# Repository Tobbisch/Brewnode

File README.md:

# Brewnode
Cheap IO node for taking in values to a Siemens PLC

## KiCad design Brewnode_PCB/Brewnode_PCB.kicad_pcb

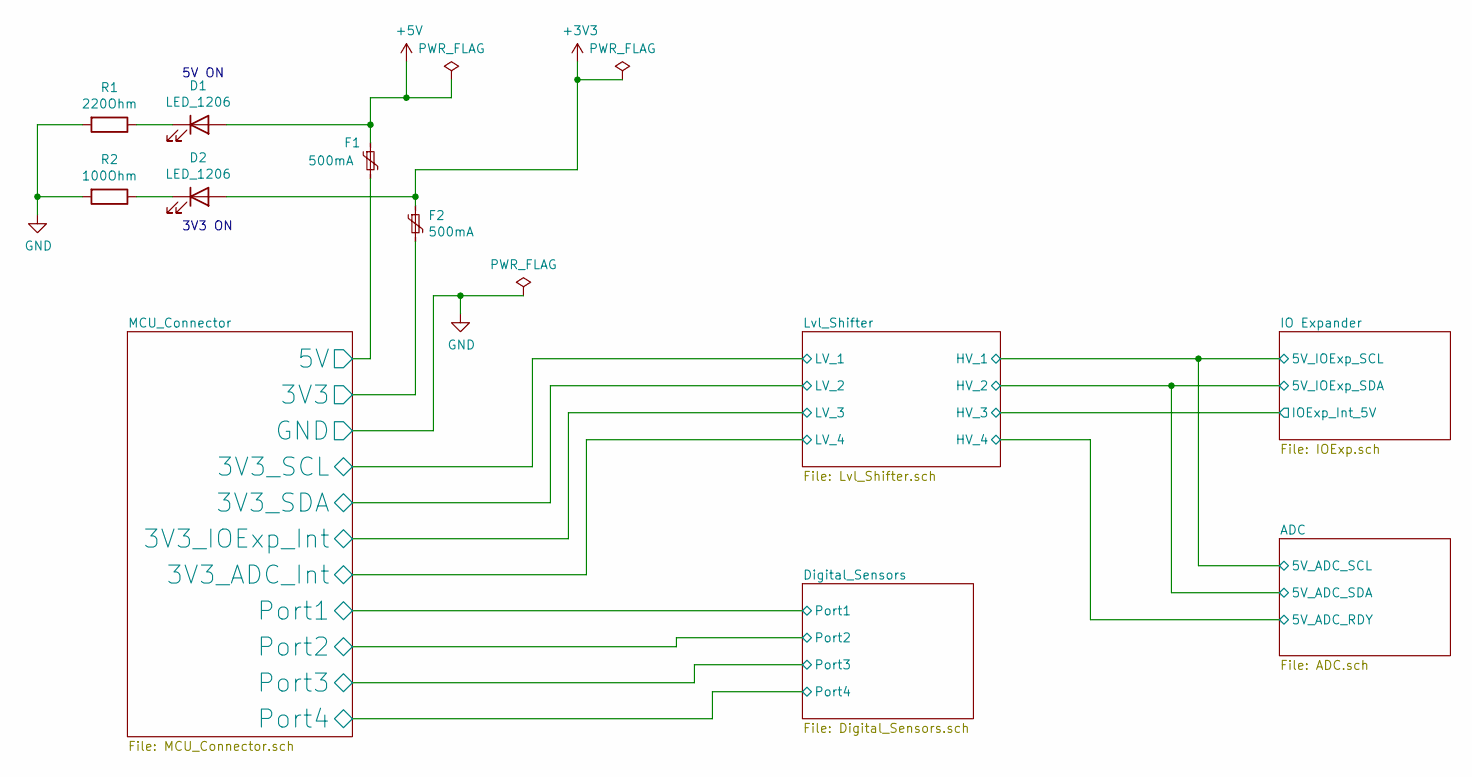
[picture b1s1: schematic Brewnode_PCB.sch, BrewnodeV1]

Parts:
D1, D2: LED_1206; LED_1206_3216Metric; LCSC C125085
F1, F2: 500mA; Fuse_0402_1005Metric; LCSC C206945
R1: 220Ohm; R_0805_2012Metric_Pad1.15x1.40mm_HandSolder; LCSC C17557
R2: 100Ohm; R_0805_2012Metric_Pad1.15x1.40mm_HandSolder; LCSC C17408

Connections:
/MCU_Connector/3V3: F2.2; also elsewhere on the board
/MCU_Connector/5V: F1.2; also elsewhere on the board
GND: R1.2, R2.2; also elsewhere on the board
unnamed: D1.1 (K), R1.1
unnamed: D2.1 (K), R2.1

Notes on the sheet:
5V ON
3V3 ON

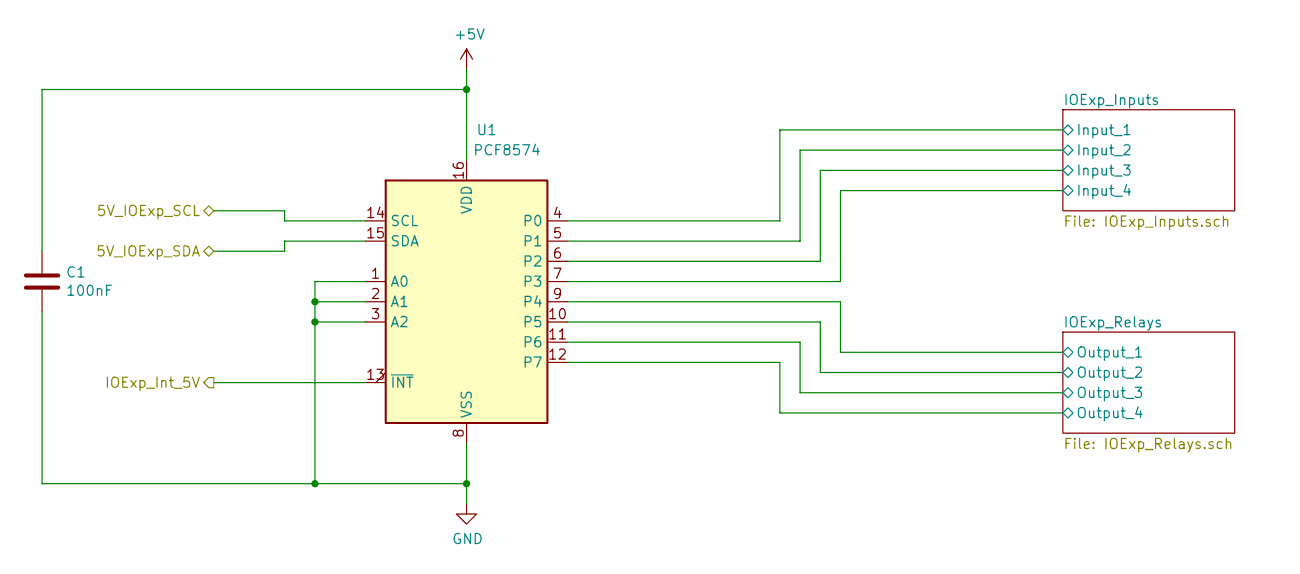
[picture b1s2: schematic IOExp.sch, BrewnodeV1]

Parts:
C1: 100nF; C_0402_1005Metric; LCSC C1525
U1: PCF8574; SOIC-16W_7.5x10.3mm_P1.27mm; LCSC C7605

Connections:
/ADC/5V_ADC_SCL: U1.14 (SCL); also elsewhere on the board
/ADC/5V_ADC_SDA: U1.15 (SDA); also elsewhere on the board
/IO Expander/IOExp_Inputs/Input_1: U1.4 (P0); also elsewhere on the board
/IO Expander/IOExp_Inputs/Input_2: U1.5 (P1); also elsewhere on the board
/IO Expander/IOExp_Inputs/Input_3: U1.6 (P2); also elsewhere on the board
/IO Expander/IOExp_Inputs/Input_4: U1.7 (P3); also elsewhere on the board
/IO Expander/IOExp_Relays/Output_1: U1.9 (P4); also elsewhere on the board
/IO Expander/IOExp_Relays/Output_2: U1.10 (P5); also elsewhere on the board
/IO Expander/IOExp_Relays/Output_3: U1.11 (P6); also elsewhere on the board
/IO Expander/IOExp_Relays/Output_4: U1.12 (P7); also elsewhere on the board
/Lvl_Shifter/HV_3: U1.13 (~INT~); also elsewhere on the board
GND: C1.2, U1.1 (A0), U1.2 (A1), U1.3 (A2), U1.8 (VSS); also elsewhere on the board

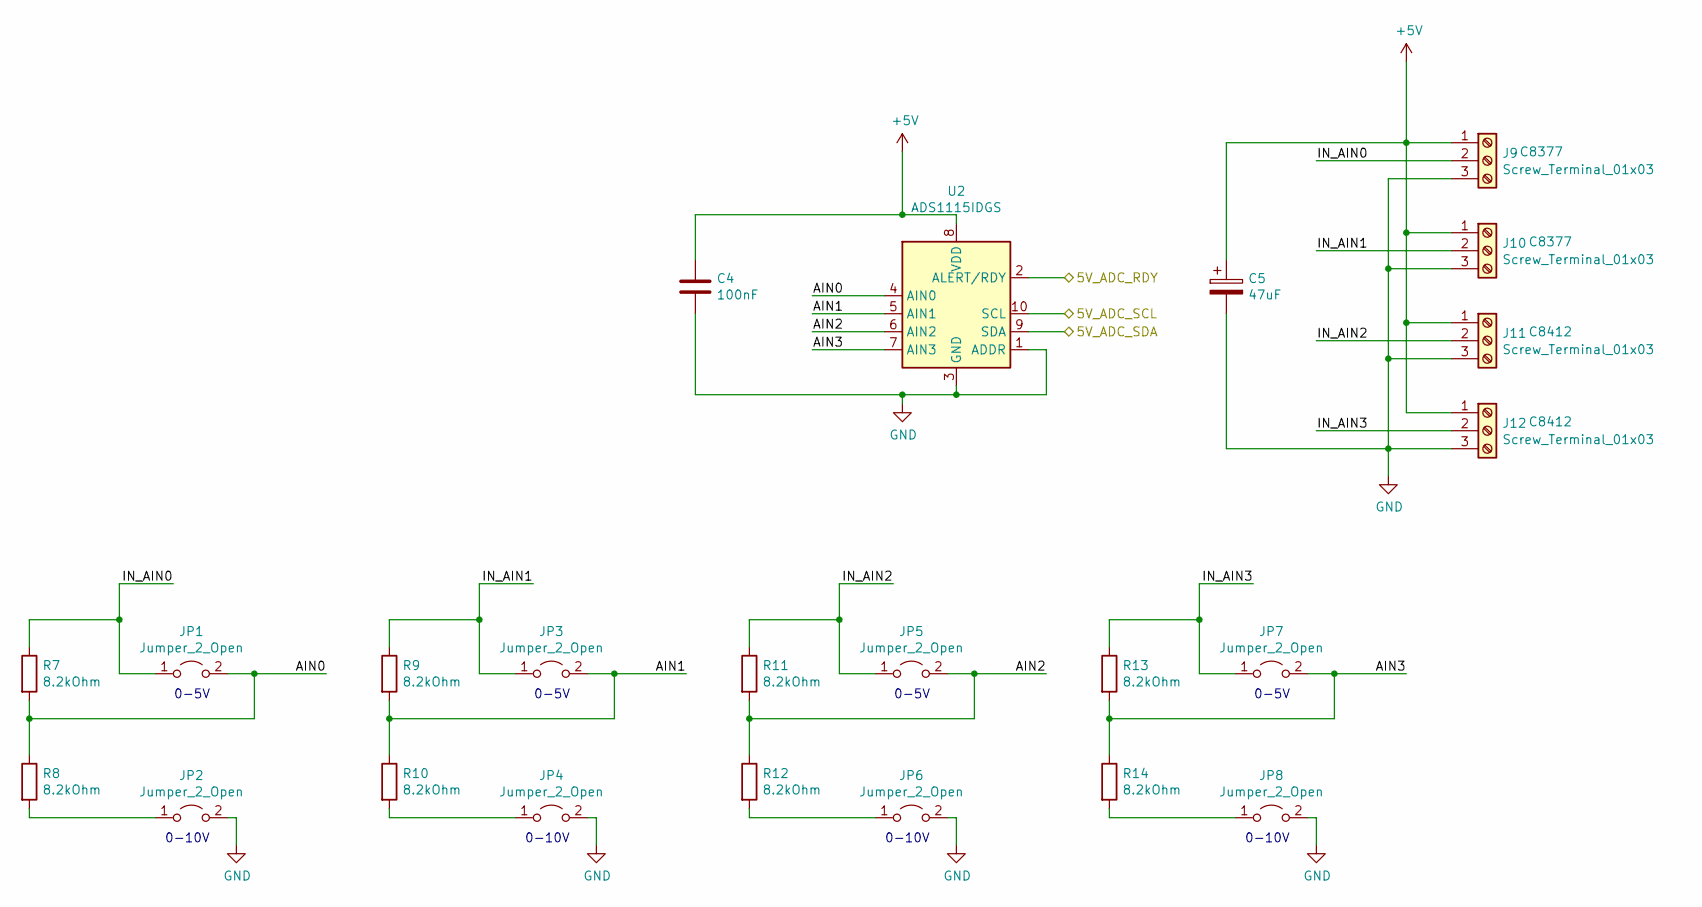
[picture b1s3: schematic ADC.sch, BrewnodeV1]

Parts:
C4: 100nF; C_0402_1005Metric; LCSC C1525
C5: 47uF; CP_Elec_6.3x5.3; LCSC C249778
J9, J10: Screw_Terminal_01x03; PhoenixContact_MSTBA_2,5_3-G-5,08_1x03_P5.08mm_Horizontal; LCSC C8377
J11, J12: Screw_Terminal_01x03; PhoenixContact_MSTBVA_2,5_3-G-5,08_1x03_P5.08mm_Vertical; LCSC C8412
JP1, JP2, JP3, JP4, JP5, JP6, JP7, JP8: Jumper_2_Open; PinHeader_1x02_P2.54mm_Vertical
R7, R8, R9, R10, R11, R12, R13, R14: 8.2kOhm; R_0805_2012Metric_Pad1.15x1.40mm_HandSolder; LCSC C407435
U2: ADS1115IDGS; VSSOP-10_3x3mm_P0.5mm; LCSC C37593

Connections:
/ADC/5V_ADC_RDY: U2.2 (ALERT/RDY); also elsewhere on the board
/ADC/5V_ADC_SCL: U2.10 (SCL); also elsewhere on the board
/ADC/5V_ADC_SDA: U2.9 (SDA); also elsewhere on the board
/ADC/AIN0: JP1.2 (B), R7.2, R8.1, U2.4 (AIN0)
/ADC/AIN1: JP3.2 (B), R9.2, R10.1, U2.5 (AIN1)
/ADC/AIN2: JP5.2 (B), R11.2, R12.1, U2.6 (AIN2)
/ADC/AIN3: JP7.2 (B), R13.2, R14.1, U2.7 (AIN3)
/ADC/IN_AIN0: J9.2, JP1.1 (A), R7.1
/ADC/IN_AIN1: J10.2, JP3.1 (A), R9.1
/ADC/IN_AIN2: J11.2, JP5.1 (A), R11.1
/ADC/IN_AIN3: J12.2, JP7.1 (A), R13.1
GND: C4.2, C5.2, J9.3, J10.3, J11.3, J12.3, JP2.2 (B), JP4.2 (B), JP6.2 (B), JP8.2 (B), U2.1 (ADDR), U2.3 (GND); also elsewhere on the board
unnamed: JP2.1 (A), R8.2
unnamed: JP4.1 (A), R10.2
unnamed: JP6.1 (A), R12.2
unnamed: JP8.1 (A), R14.2

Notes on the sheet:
0-5V
0-10V

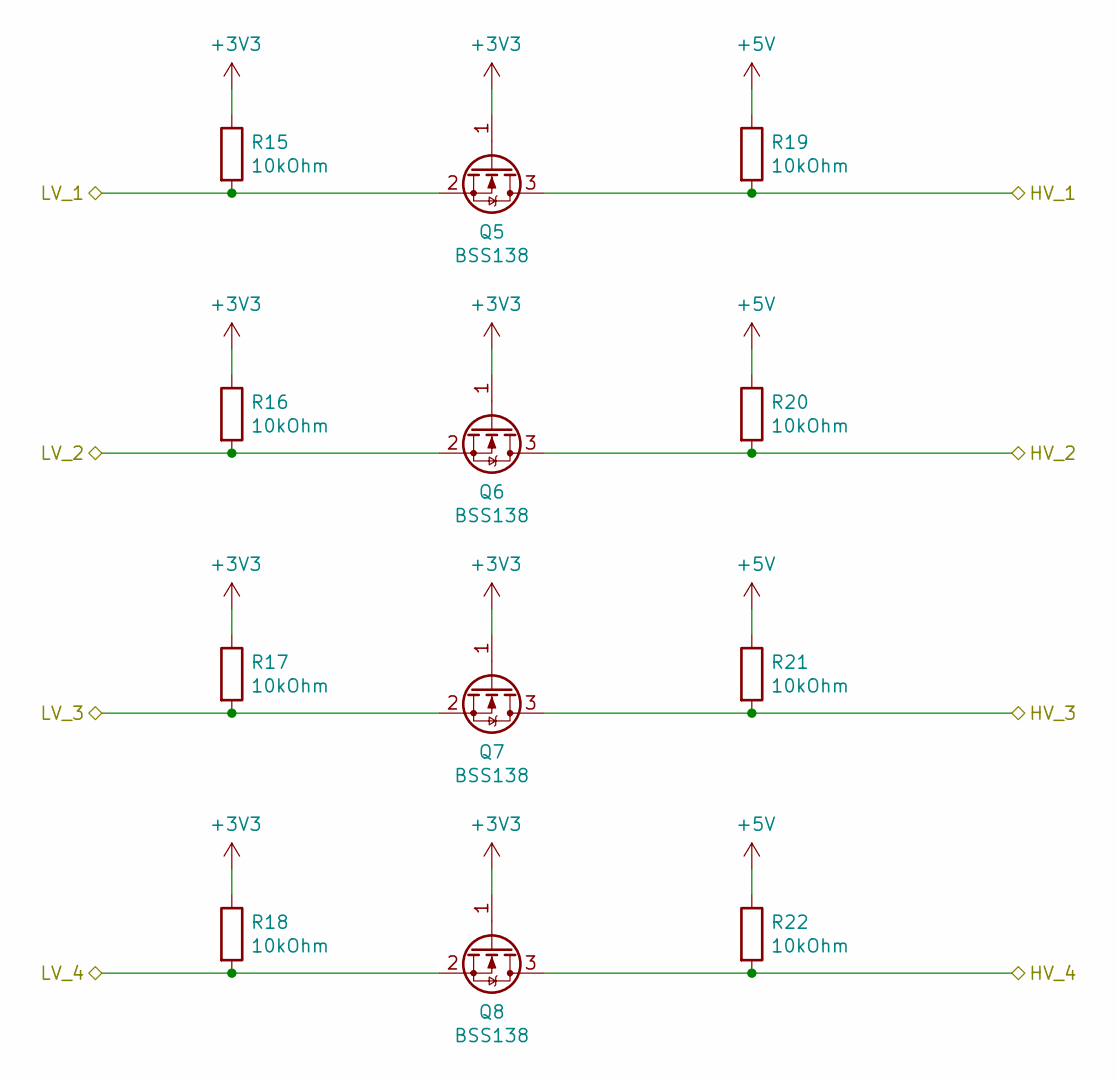
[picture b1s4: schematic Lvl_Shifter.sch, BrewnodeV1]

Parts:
Q5, Q6, Q7, Q8: BSS138; SOT-23; LCSC C52895
R15, R16, R17, R18, R19, R20, R21, R22: 10kOhm; R_0805_2012Metric_Pad1.15x1.40mm_HandSolder; LCSC C17414

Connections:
/ADC/5V_ADC_RDY: Q8.3 (D), R22.2; also elsewhere on the board
/ADC/5V_ADC_SCL: Q5.3 (D), R19.2; also elsewhere on the board
/ADC/5V_ADC_SDA: Q6.3 (D), R20.2; also elsewhere on the board
/Lvl_Shifter/HV_3: Q7.3 (D), R21.2; also elsewhere on the board
/MCU_Connector/3V3_ADC_Int: Q8.2 (S), R18.2; also elsewhere on the board
/MCU_Connector/3V3_IOExp_Int: Q7.2 (S), R17.2; also elsewhere on the board
/MCU_Connector/3V3_SCL: Q5.2 (S), R15.2; also elsewhere on the board
/MCU_Connector/3V3_SDA: Q6.2 (S), R16.2; also elsewhere on the board

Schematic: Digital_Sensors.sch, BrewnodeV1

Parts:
C6: 47uF; CP_Elec_6.3x5.3; LCSC C249778
J13, J14: Screw_Terminal_01x03; PhoenixContact_MSTBA_2,5_3-G-5,08_1x03_P5.08mm_Horizontal; LCSC C8377
J15, J16: Screw_Terminal_01x03; PhoenixContact_MSTBVA_2,5_3-G-5,08_1x03_P5.08mm_Vertical; LCSC C8412
R23, R24, R25, R26: 4.7kOhm; R_0805_2012Metric_Pad1.15x1.40mm_HandSolder; LCSC C17673

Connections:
/Digital_Sensors/Port1: J13.2, R23.2; also elsewhere on the board
/Digital_Sensors/Port2: J14.2, R24.2; also elsewhere on the board
/Digital_Sensors/Port3: J15.2, R25.2; also elsewhere on the board
/Digital_Sensors/Port4: J16.2, R26.2; also elsewhere on the board
GND: C6.2, J13.3, J14.3, J15.3, J16.3; also elsewhere on the board

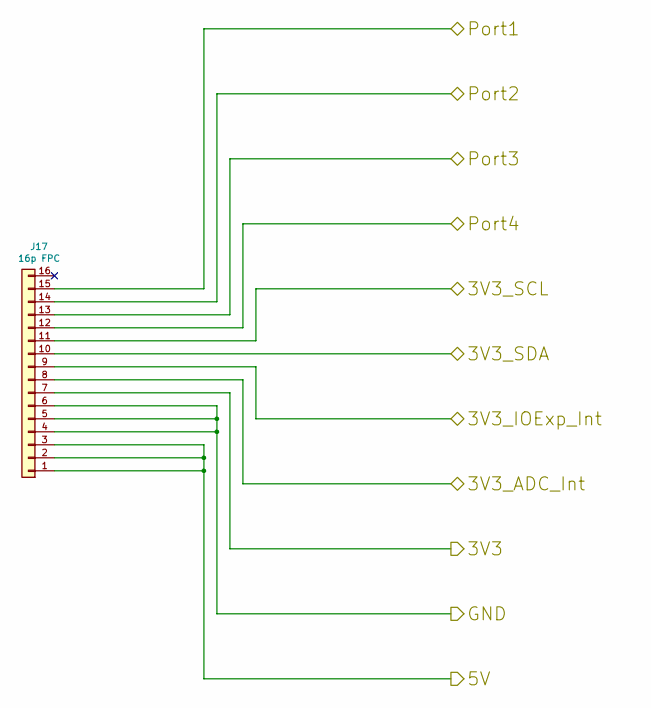
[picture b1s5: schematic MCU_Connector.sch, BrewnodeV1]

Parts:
J17: 16p FPC; Hirose_FH34_FPC_16; LCSC C324725

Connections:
/Digital_Sensors/Port1: J17.15; also elsewhere on the board
/Digital_Sensors/Port2: J17.14; also elsewhere on the board
/Digital_Sensors/Port3: J17.13; also elsewhere on the board
/Digital_Sensors/Port4: J17.12; also elsewhere on the board
/MCU_Connector/3V3: J17.7; also elsewhere on the board
/MCU_Connector/3V3_ADC_Int: J17.8; also elsewhere on the board
/MCU_Connector/3V3_IOExp_Int: J17.9; also elsewhere on the board
/MCU_Connector/3V3_SCL: J17.11; also elsewhere on the board
/MCU_Connector/3V3_SDA: J17.10; also elsewhere on the board
/MCU_Connector/5V: J17.1, J17.2, J17.3; also elsewhere on the board
GND: J17.4, J17.5, J17.6; also elsewhere on the board

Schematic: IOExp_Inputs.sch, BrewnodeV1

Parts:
C2: 47uF; CP_Elec_6.3x5.3; LCSC C249778
J1, J2: Screw_Terminal_01x03; PhoenixContact_MSTBA_2,5_3-G-5,08_1x03_P5.08mm_Horizontal; LCSC C8377
J3, J4: Screw_Terminal_01x03; PhoenixContact_MSTBVA_2,5_3-G-5,08_1x03_P5.08mm_Vertical; LCSC C8412
R27, R28, R29, R30: 10kOhm; R_0805_2012Metric_Pad1.15x1.40mm_HandSolder; LCSC C17414

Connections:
/IO Expander/IOExp_Inputs/Input_1: J1.2, R27.2; also elsewhere on the board
/IO Expander/IOExp_Inputs/Input_2: J2.2, R28.2; also elsewhere on the board
/IO Expander/IOExp_Inputs/Input_3: J3.2, R29.2; also elsewhere on the board
/IO Expander/IOExp_Inputs/Input_4: J4.2, R30.2; also elsewhere on the board
GND: C2.2, J1.3, J2.3, J3.3, J4.3; also elsewhere on the board

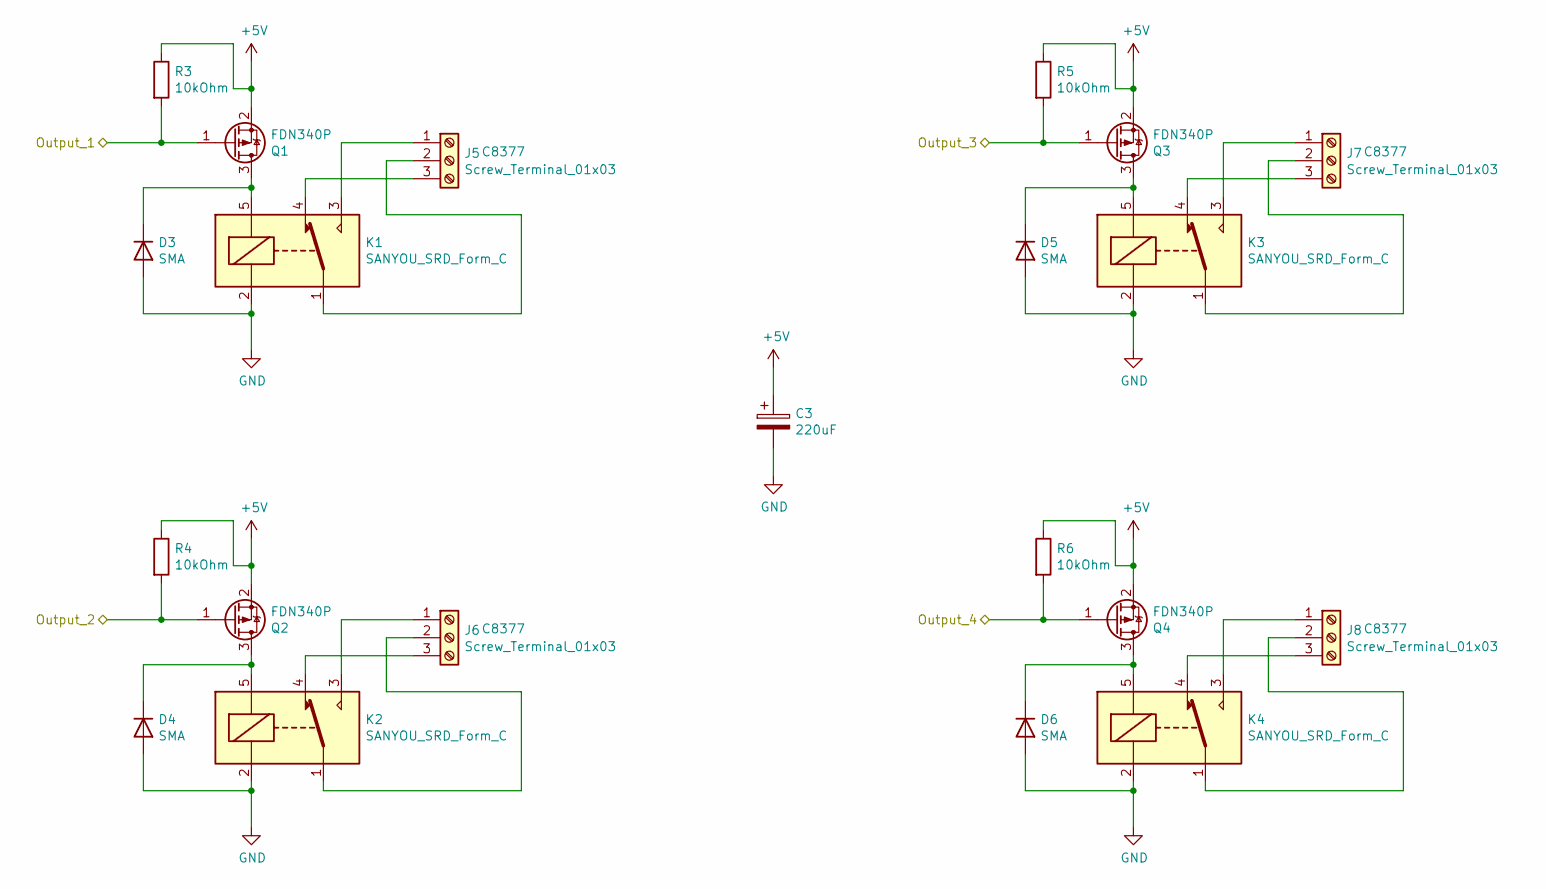
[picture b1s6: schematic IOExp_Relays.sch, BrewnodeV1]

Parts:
C3: 220uF; CP_Elec_8x10; LCSC C249801
D3, D4, D5, D6: SMA; D_SMA-SMB_Universal_Handsoldering; LCSC C95872
J5, J6, J7, J8: Screw_Terminal_01x03; PhoenixContact_MSTBA_2,5_3-G-5,08_1x03_P5.08mm_Horizontal; LCSC C8377
K1, K2, K3, K4: SANYOU_SRD_Form_C; Relay_SPDT_SANYOU_SRD_Series_Form_C; LCSC C35449
Q1, Q2, Q3, Q4: FDN340P; SOT-23; LCSC C75469
R3, R4, R5, R6: 10kOhm; R_0805_2012Metric_Pad1.15x1.40mm_HandSolder; LCSC C17414

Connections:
/IO Expander/IOExp_Relays/Output_1: Q1.1 (G), R3.2; also elsewhere on the board
/IO Expander/IOExp_Relays/Output_2: Q2.1 (G), R4.2; also elsewhere on the board
/IO Expander/IOExp_Relays/Output_3: Q3.1 (G), R5.2; also elsewhere on the board
/IO Expander/IOExp_Relays/Output_4: Q4.1 (G), R6.2; also elsewhere on the board
GND: C3.2, D3.2 (A), D4.2 (A), D5.2 (A), D6.2 (A), K1.2, K2.2, K3.2, K4.2; also elsewhere on the board
unnamed: D3.1 (K), K1.5, Q1.3 (D)
unnamed: D4.1 (K), K2.5, Q2.3 (D)
unnamed: D5.1 (K), K3.5, Q3.3 (D)
unnamed: D6.1 (K), K4.5, Q4.3 (D)
unnamed: J5.1, K1.3
unnamed: J5.2, K1.1
unnamed: J5.3, K1.4
unnamed: J6.1, K2.3
unnamed: J6.2, K2.1
unnamed: J6.3, K2.4
unnamed: J7.1, K3.3
unnamed: J7.2, K3.1
unnamed: J7.3, K3.4
unnamed: J8.1, K4.3
unnamed: J8.2, K4.1
unnamed: J8.3, K4.4

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
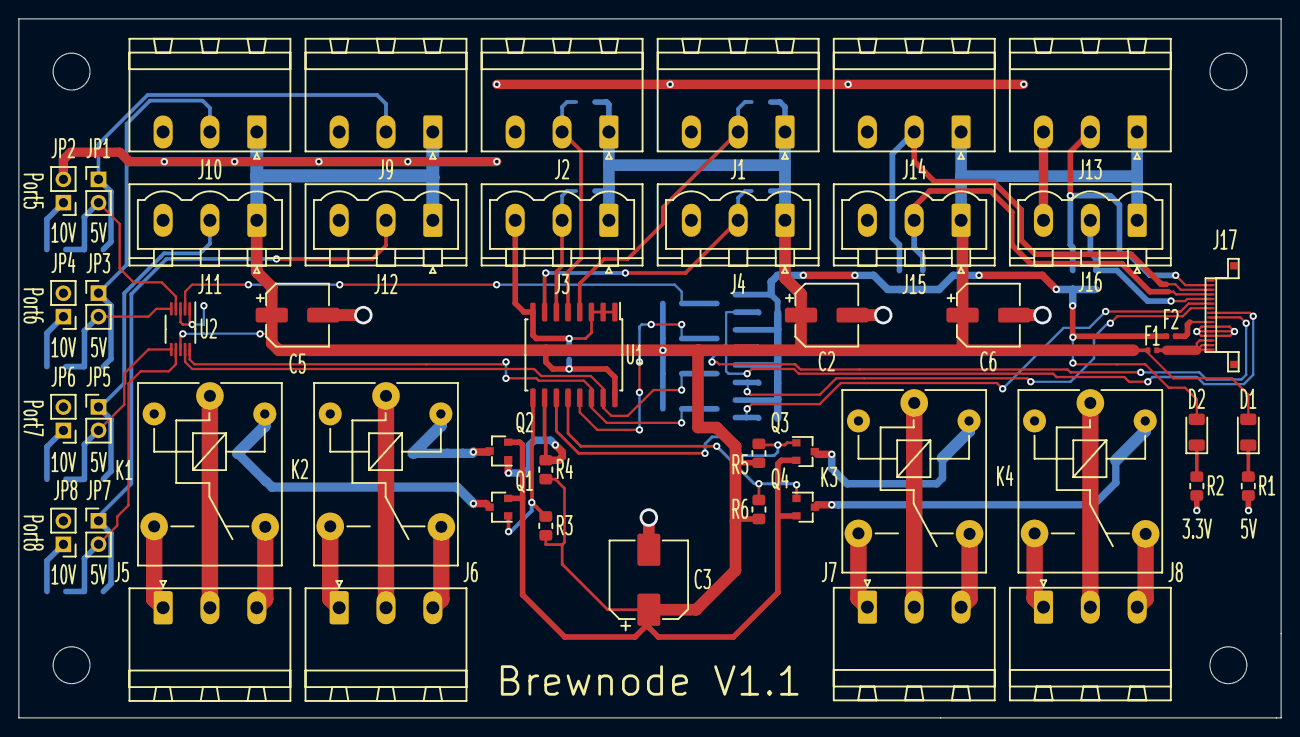
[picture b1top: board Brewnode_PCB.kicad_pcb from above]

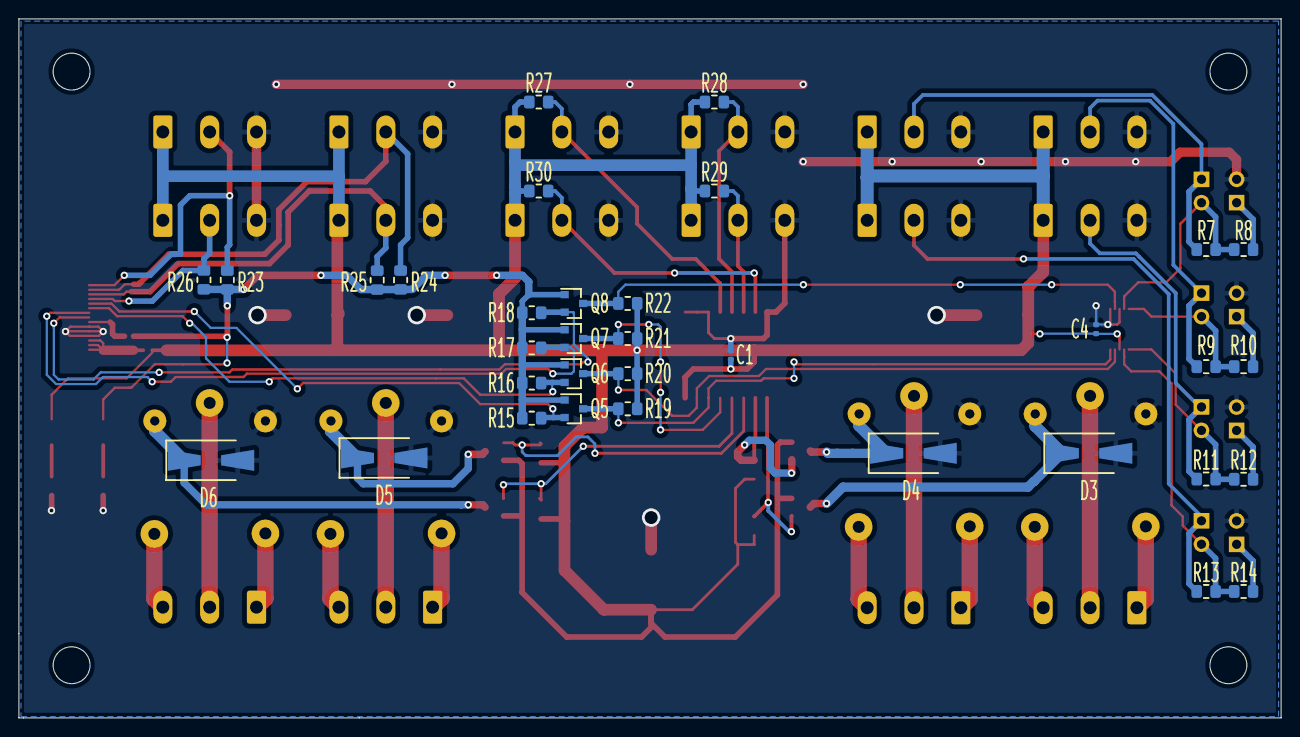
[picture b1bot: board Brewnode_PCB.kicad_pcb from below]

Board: 2 copper layers, 136.9 x 75.8 mm, 83 parts (34 on the bottom side), 55 nets.

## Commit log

2020-09-14 Added PCB
2020-09-14 PCB Work
2020-09-14 More PCB Work
2020-09-15 More PCB Sch work
2020-09-17 Done PCB Sch Work
2020-09-18 More PCB Pcb work
2020-09-21 PCB V1 To production
2020-09-22 PCB_V1 Sent to production
2020-09-24 PCB Corrected library
2020-09-24 Update fp-info-cache
2020-10-15 Sch + PCB V1.1
    Corrected FDN340 P-FET Pinout.
    Added 5V, 3V3 Description in silkscreen for indication D1, D2
